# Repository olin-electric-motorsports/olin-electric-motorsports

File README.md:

<h1 align="center">
	
</h1>

Welcome to the Olin Electric Motorsports monorepo. This is the home for all of our
electrical, firmware, and software work.

This document will help you get started contributing and walk you through
important steps for collaborating with teammates.

## Getting Started

### For new members:
Make sure you have a GitHub account. If you don't, create one on [GitHub](github.com) (this website). Make sure to save your username, email, and password. This will be useful in the next step. Once you have an account, STOP, and ask a lead/senior engineer to add you to the `olin-electric-motorsports` org.

Once you've successfully installed Ubuntu, have a GitHub account, and have ben added as an org member: on your computer, open a terminal (press the Windows key and type `term`, then hit `Enter`).

Install `git` on your computer if it's not already.
```shell
sudo apt install git -y
```

Also install python3.10
```shell
sudo apt update && sudo apt install python3.10
```

One last Python library...
```shell
sudo apt-get install python3-distutils
```

### Linking a Computer to your Account
We need to connect your GitHub account to your computer's specific git instance \(created by the command you just ran\). We do this for safety: someone pretending to be you can't add code to our repo!
1. Set your username:
```shell
git config --global user.name 'your username here'
```

2. Set your email address:
```shell
git config --global user.email 'your email here'
```

3. Create the SSH Key \(essentially a super crazy passord\). When you’re prompted to "Enter a file in which to save the key," press `Enter`. This accepts the default file location. At the password prompt, hit `Enter` again.
```shell
ssh-keygen -t ed25519 -C "your_email@example.com"
```

4. To see your SSH Key, run the following command. Copy the whole contents of the output to your clipboard (you won't be able to copy or paste in the terminal using ctrl+c and ctrl+v, instead use ctrl+shift+c and ctrl+shift+v or right-click to do it graphically).
```shell
cat ~/.ssh/id_ed25519.pub
```

5. In your github page, go to your profile \(Top Right\) > `settings` > `SSH and GPG Keys`. Click on the green `New SSH Key` button. Title your key as `Olin Computer` and paste in your SSH key. Finally, click the green `Add SSH Key` button. Nearly done!
6. Test your ssh connection by using the command below. Type `yes` when prompted. You've done this step correctly if you see something along the lines of `Hi "username"! You've successfully authenticated, but GitHub does not provide shell access.`
```shell
ssh -T git@github.com
```
### Creating your OEM environment
Clone this repository into a folder of your choice (many people
choose to put it in `~/Documents`.

```shell
cd ~/Documents
git clone git@github.com:olin-electric-motorsports/olin-electric-motorsports.git
```

Once you have it, cd into the repo and install the KiCad Git filters (a set of rules that remove temp files that can cause clutter):

```shell
cd olin-electric-motorsports/
./scripts/install_kicad_git_filters.sh
```

You'll also want to have the KiCad Git Hooks to generate our symbol libraries. These hooks run every time you push or pull and allow multiple users to add symbols/footprints to our KiCAD library.

```shell
./scripts/install_kicad_git_hooks.sh
```

### Installing AVR and tools
Next, install the AVR toolchain:

```shell
sudo apt install gcc-avr avrdude avr-libc binutils-avr gdb-avr
```

### Installing Cantools
You need to be able to hear to our MCUs on the car!
```shell
pip3 install cantools
sudo apt install can-utils
```

### Installing Bazel

Next, install Bazelisk. Run this massive blob and you should be good to go.

```shell
sudo apt install apt-transport-https curl gnupg -y
curl -fsSL https://bazel.build/bazel-release.pub.gpg | gpg --dearmor >bazel-archive-keyring.gpg
sudo mv bazel-archive-keyring.gpg /usr/share/keyrings
echo "deb [arch=amd64 signed-by=/usr/share/keyrings/bazel-archive-keyring.gpg] https://storage.googleapis.com/bazel-apt stable jdk1.8" | sudo tee /etc/apt/sources.list.d/bazel.list
sudo apt install bazel-5.4.0
```

You should now be able to run the following without error (after changing your directory to be in
the `olin-electric-motorsports` folder):

```shell
bazel build --config=16m1 //examples/16M1/blinky -c opt
```

> [!NOTE]
> If you get an error message stating 'env: python: No such file or directory', ensure that the PATH environment variable is properly established. This can be done by adding the file to your .bashrc file:
> ```
> export PATH=$PATH:/usr/local/bin
> ```

### KiCad Setup

To install KiCad on Ubuntu, run the following: Type `Y` when prompted.

```shell
sudo add-apt-repository --yes ppa:kicad/kicad-8.0-releases
sudo apt update
sudo apt install --install-recommends kicad
```

Open KiCad (windows key and type KiCAD) Click on the Blue App (always do this when opening Kicad - otherwise you can corrupt files!). Hit `Enter` if asked about settings imports and auto-updates for add-ons.
From the top bar, open _Preferences > Configure Paths..._. Add a new row to the table using the plus button (you will have to fill out TWO fields... shown below):

Name | Path
-----|-----
OEM\_DIR|`/home/your-username/Documents/olin-electric-motorsports`

Click `OK`, then again from the top bar, open _Preferences > Manage Symbol Libraries ..._.
Same deal as before with the new line at the bottom, new values though this time:

Name | Path
-----|-----
OEM |`${OEM_DIR}/parts/schematic/oem.kicad_sym`

> [!WARNING]
> If you get an error, you either typed something incorrectly or haven't generated the OEM symbol library ever before.
> To generate:
> 1. navigate to the base `olin-electric-motorsports` directory in a terminal.
> 2. run python3 tools/symbols/convert.py symbols2library
> 3. path to symbol files: parts/schematic/oem
> 4. path to library file: parts/schematic/oem.kicad_sym

Click `OK`, then again from the top bar, open _Preferences > Manage Footprint Libraries ..._.
3rd time's the magic one, plus button, add the values in the table below.

Name | Path
-----|-----
OEM |`${OEM_DIR}/parts/oem.pretty`

where `your-username` is the username on your computer.
If you cloned our repository into a different directory than the `~/Documents` folder, this is just an absolute path to the repo.

Visit [this page](https://www.kicad.org/download/) to find instructions for
downloading KiCad for other operating systems.

## Integration Resources
### Flashing to microcontrollers

> [!CAUTION]
> Take care to plug in the programmer correctly. If you insert it the wrong way, you have the potential to reverse-bias sensitive electronics (you could smoke them)!

To flash (program) an ATMEGA16m1 microcontroller, use a variation of the following command:
```shell
need to insert example flashing command here
```

To flash (program) an ATMEGA16m1 microcontroller using the btldr (remote CAN flashing), use a variation of the following command:
```shell
need to insert example can flashing command here
```

### Viewing CAN data/the canviewer
First, plug a CAN-to-USB dongle into your computer and connect CAN+ and CAN- to the car or test platform's CAN port.

To initalize the dongle, run the following command:
```shell
need to insert example can init command here
```

### Cantools
1. `candump`: A tool for streaming CAN frames as they are sent. Useful for short captures or slow data.
2. `cansniffer`: Similar to candump, but messages with the same ID replace each other for easier viewing (a table).
3. `cansend`: Use this tool to send CAN frames from your computer. CAN (oh the puns will never end) be helpful when debugging boards or to program modules like the motor controller or G-Meter.

### CANViewer
OEM has designed a custom Python CAN GUI to monitor the car's state.
Type the following command to run the viewer.
```shell
need to insert CANViewer command here.
```

### Contributing

If you are working on a new project, the first step is to make sure you have the
latest code:

```shell
git pull origin main
```

### Onboarding stop here...

Next, create your feature branch (only do this once you have a project!):

```shell
git switch -c your-username/feature-name origin/main
```

Now, you can start working on code, committing on your branch, and eventually
opening up a pull request to `main`.

New projects should be placed into a folder within the `//projects` directory
(for instance, `//projects/hitl/`. Hardware and firmware that run on MKV or MKVI
should go in the proper subfolder within `//vehicle`.

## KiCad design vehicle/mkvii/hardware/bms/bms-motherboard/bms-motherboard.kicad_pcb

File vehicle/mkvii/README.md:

# MKVII

The development of boards for the Mark VII car will go in this folder.
Here's to a great year everyone!

Rev. 1: Hardware complete as of 3/9/2025! Subteam folders have their boards inside.
Rev. 2: Software build-out in progress. As of 3/9/2025 the basic folder structure exists!

Useful commands:
1. Setting up a CANnable: `sudo ip link set can0 up type can bitrate 500000`
2. Dumping all CAN commands: `candump can0`
3. Dumping specific commands with a specific address (XXX): `candump can0,XXX:7ff`
4. Quickly viewing many CAN messages in a readable way: `cansniffer can0`
5. using canviewer: `bazel run //projects/canviewer -- -b socketcan -c can0`
6. Flashing an ATMEGA: `SET_FUSES=1 bazel run --config=16m1 -c opt //examples/blinky -- -c usbasp` IF FLASH FAILS, BOARD IS MADE INCORRECTLY. Use `usbasp` for the small programmers, `avrispmkII` for the large blue ones. SET_FUSES=1 required for first flash only.

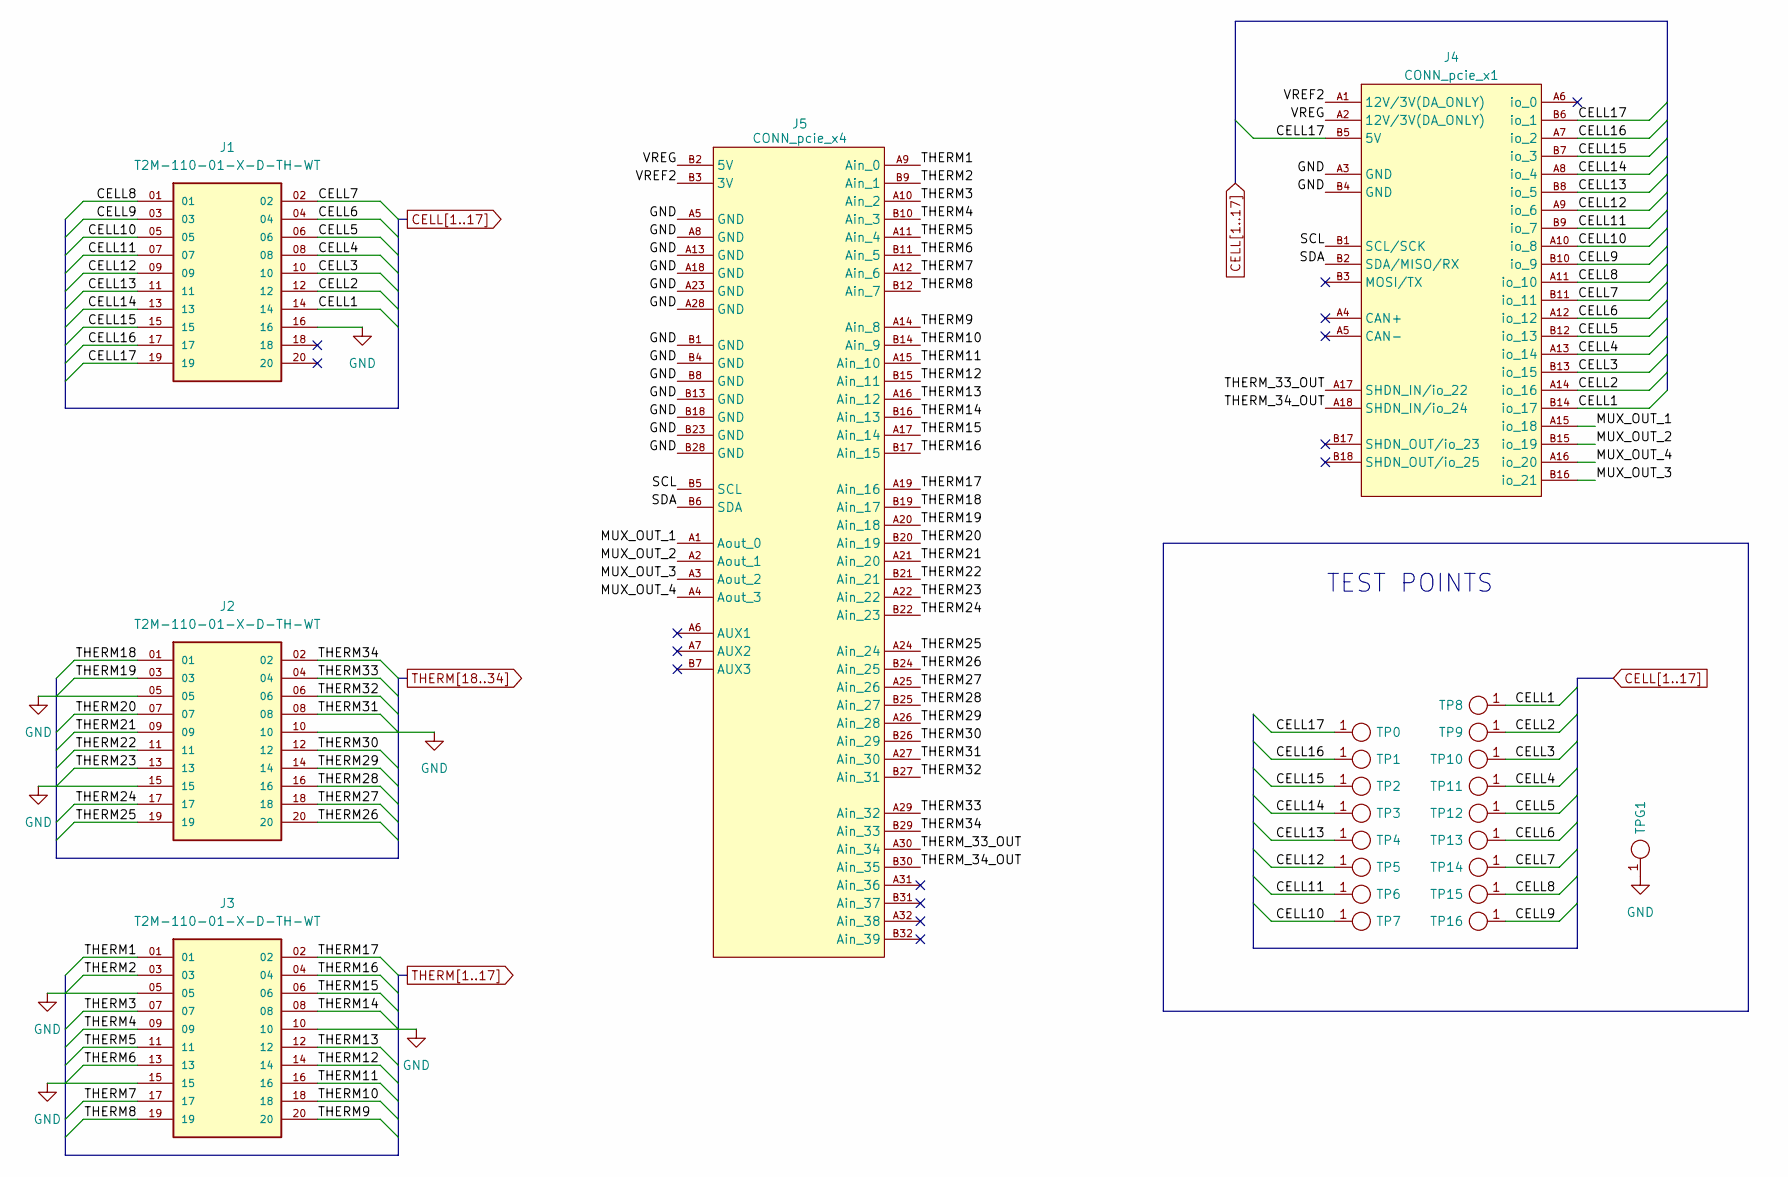
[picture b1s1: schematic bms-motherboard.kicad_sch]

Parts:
J1, J2, J3: T2M-110-01-X-D-TH-WT; SAMTEC_T2M-110-01-X-D-TH-WT; PARTREV AH
J4: CONN_pcie_x1; te_pcie_x1_connector
J5: CONN_pcie_x4; te_pcie_x4_connector
TP0, TP1, TP2, TP3, TP4, TP5, TP6, TP7, TP8, TP9, TP10, TP11, TP12, TP13, TP14, TP15, TP16: TP_SMD; Test_Point_SMD; MPN 5019
TPG1: TP_SMD; Test_Point_SMD; MPN 5019

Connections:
/MUX_OUT_1: J4.A15 (io_18), J5.A1 (Aout_0)
/MUX_OUT_2: J4.B15 (io_19), J5.A2 (Aout_1)
/MUX_OUT_3: J4.B16 (io_21), J5.A3 (Aout_2)
/MUX_OUT_4: J4.A16 (io_20), J5.A4 (Aout_3)
/SCL: J4.B1 (SCL/SCK), J5.B5 (SCL)
/SDA: J4.B2 (SDA/MISO/RX), J5.B6 (SDA)
/THERM_33_OUT: J4.A17 (SHDN_IN/io_22), J5.A30 (Ain_34)
/THERM_34_OUT: J4.A18 (SHDN_IN/io_24), J5.B30 (Ain_35)
/VREF2: J4.A1 (12V/3V(DA_ONLY)), J5.B3 (3V)
/VREG: J4.A2 (12V/3V(DA_ONLY)), J5.B2 (5V)
CELL1: J1.14, J4.B14 (io_17), TP8.1
CELL2: J1.12, J4.A14 (io_16), TP9.1
CELL3: J1.10, J4.B13 (io_15), TP10.1
CELL4: J1.08, J4.A13 (io_14), TP11.1
CELL5: J1.06, J4.B12 (io_13), TP12.1
CELL6: J1.04, J4.A12 (io_12), TP13.1
CELL7: J1.02, J4.B11 (io_11), TP14.1
CELL8: J1.01, J4.A11 (io_10), TP15.1
CELL9: J1.03, J4.B10 (io_9), TP16.1
CELL10: J1.05, J4.A10 (io_8), TP7.1
CELL11: J1.07, J4.B9 (io_7), TP6.1
CELL12: J1.09, J4.A9 (io_6), TP5.1
CELL13: J1.11, J4.B8 (io_5), TP4.1
CELL14: J1.13, J4.A8 (io_4), TP3.1
CELL15: J1.15, J4.B7 (io_3), TP2.1
CELL16: J1.17, J4.A7 (io_2), TP1.1
CELL17: J1.19, J4.B5 (5V), J4.B6 (io_1), TP0.1
GND: J1.16, J2.05, J2.10, J2.15, J3.05, J3.10, J3.15, J4.A3 (GND), J4.B4 (GND), J5.A5 (GND), J5.A8 (GND), J5.A13 (GND), J5.A18 (GND), J5.A23 (GND), J5.A28 (GND), J5.B1 (GND), J5.B4 (GND), J5.B8 (GND), J5.B13 (GND), J5.B18 (GND), J5.B23 (GND), J5.B28 (GND), TPG1.1; also elsewhere on the board
THERM1: J3.01, J5.A9 (Ain_0)
THERM2: J3.03, J5.B9 (Ain_1)
THERM3: J3.07, J5.A10 (Ain_2)
THERM4: J3.09, J5.B10 (Ain_3)
THERM5: J3.11, J5.A11 (Ain_4)
THERM6: J3.13, J5.B11 (Ain_5)
THERM7: J3.17, J5.A12 (Ain_6)
THERM8: J3.19, J5.B12 (Ain_7)
THERM9: J3.20, J5.A14 (Ain_8)
THERM10: J3.18, J5.B14 (Ain_9)
THERM11: J3.16, J5.A15 (Ain_10)
THERM12: J3.14, J5.B15 (Ain_11)
THERM13: J3.12, J5.A16 (Ain_12)
THERM14: J3.08, J5.B16 (Ain_13)
THERM15: J3.06, J5.A17 (Ain_14)
THERM16: J3.04, J5.B17 (Ain_15)
THERM17: J3.02, J5.A19 (Ain_16)
THERM18: J2.01, J5.B19 (Ain_17)
THERM19: J2.03, J5.A20 (Ain_18)
THERM20: J2.07, J5.B20 (Ain_19)
THERM21: J2.09, J5.A21 (Ain_20)
THERM22: J2.11, J5.B21 (Ain_21)
THERM23: J2.13, J5.A22 (Ain_22)
THERM24: J2.17, J5.B22 (Ain_23)
THERM25: J2.19, J5.A24 (Ain_24)
THERM26: J2.20, J5.B24 (Ain_25)
THERM27: J2.18, J5.A25 (Ain_26)
THERM28: J2.16, J5.B25 (Ain_27)
THERM29: J2.14, J5.A26 (Ain_28)
THERM30: J2.12, J5.B26 (Ain_29)
THERM31: J2.08, J5.A27 (Ain_30)
THERM32: J2.06, J5.B27 (Ain_31)
THERM33: J2.04, J5.A29 (Ain_32)
THERM34: J2.02, J5.B29 (Ain_33)

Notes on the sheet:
TEST POINTS

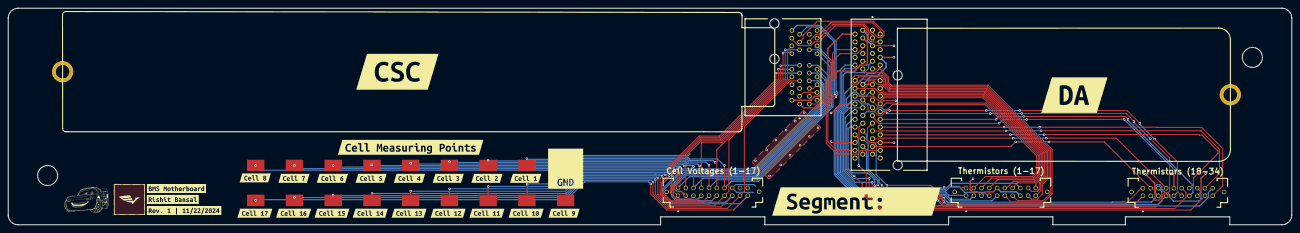
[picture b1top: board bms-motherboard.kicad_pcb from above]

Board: 2 copper layers, 331.3 x 55.9 mm, 50 parts (0 on the bottom side), 62 nets.

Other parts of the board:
H1, H2: CONN_MountingHole; PCIe_Mount
kibuzzard-6747A1EF: G***; kibuzzard-6747A1EF
kibuzzard-6747A1F5: G***; kibuzzard-6747A1F5
kibuzzard-6747A1FA: G***; kibuzzard-6747A1FA
kibuzzard-6747A20D: G***; kibuzzard-6747A20D
kibuzzard-6747A21A: G***; kibuzzard-6747A21A
kibuzzard-6747A21D: G***; kibuzzard-6747A21D
kibuzzard-6747A22C: G***; kibuzzard-6747A22C
kibuzzard-6747A22F: G***; kibuzzard-6747A22F
kibuzzard-6747A069: G***; kibuzzard-6747A069
kibuzzard-6747A200: G***; kibuzzard-6747A200
kibuzzard-6747A204: G***; kibuzzard-6747A204
kibuzzard-6747A209: G***; kibuzzard-6747A209
kibuzzard-6747A211: G***; kibuzzard-6747A211
kibuzzard-6747A215: G***; kibuzzard-6747A215
kibuzzard-6747A222: G***; kibuzzard-6747A222
kibuzzard-6747A229: G***; kibuzzard-6747A229
kibuzzard-6747A234: G***; kibuzzard-6747A234
kibuzzard-6747A319: G***; kibuzzard-6747A319
kibuzzard-6747A384: G***; kibuzzard-6747A384
kibuzzard-6747F2A5: G***; kibuzzard-6747F2A5
kibuzzard-67479DDA: G***; kibuzzard-67479DDA
kibuzzard-67479DE7: G***; kibuzzard-67479DE7
kibuzzard-67479E06: G***; kibuzzard-67479E06
kibuzzard-67479E66: G***; kibuzzard-67479E66
kibuzzard-67479E86: G***; kibuzzard-67479E86

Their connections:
GND: H2.1; also elsewhere on the board

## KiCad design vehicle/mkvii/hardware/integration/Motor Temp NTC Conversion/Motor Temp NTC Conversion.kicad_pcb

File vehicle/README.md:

# Vehicle

The boards and code for the different vehicles that the team builds will exist
in this folder.

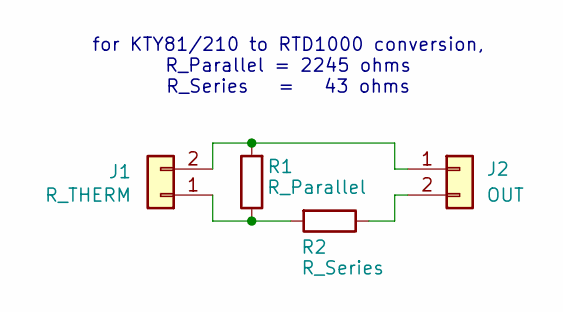
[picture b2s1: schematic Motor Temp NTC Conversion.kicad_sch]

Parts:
J1: R_THERM; Molex_Micro-Fit_3.0_43650-0215_1x02_P3.00mm_Vertical
J2: OUT; Molex_Micro-Fit_3.0_43650-0215_1x02_P3.00mm_Vertical
R1: R_Parallel; R_0603; MPN RMCF0603FT1K00
R2: R_Series; R_0603; MPN RMCF0603FT1K00

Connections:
unnamed: J1.1, R1.1, R2.2
unnamed: J1.2, J2.1, R1.2
unnamed: J2.2, R2.1

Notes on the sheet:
for KTY81/210 to RTD1000 conversion, R_Parallel = 2245 ohms R_Series = 43 ohms

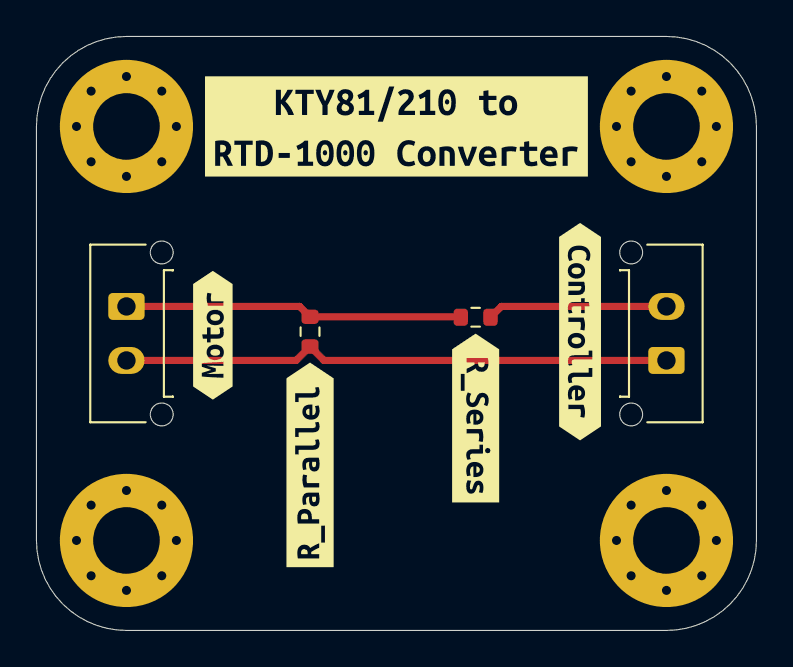
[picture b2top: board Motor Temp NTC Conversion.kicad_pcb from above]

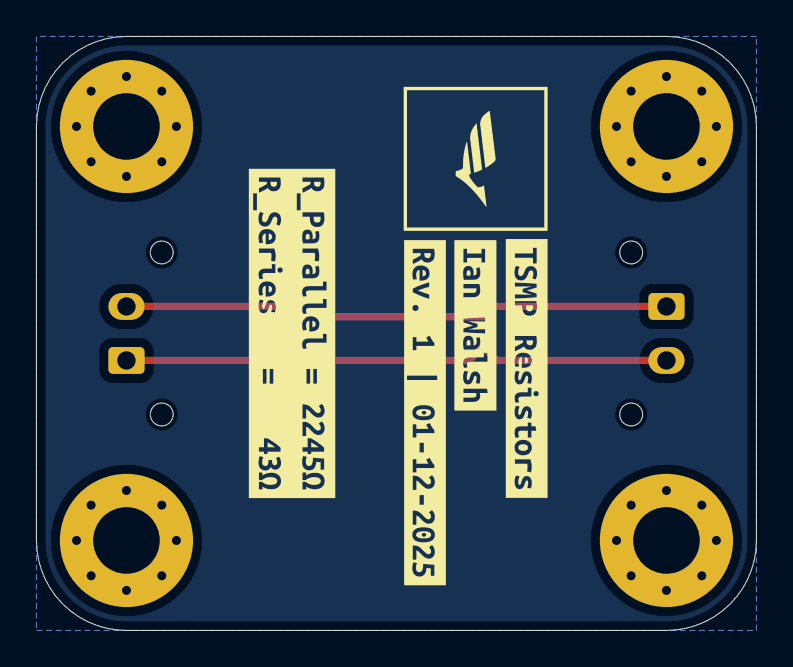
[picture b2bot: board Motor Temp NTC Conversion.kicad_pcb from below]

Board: 2 copper layers, 40.0 x 33.0 mm, 13 parts (4 on the bottom side), 3 nets.

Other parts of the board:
kibuzzard-679ED0A2: G***; kibuzzard-679ED0A2
kibuzzard-679ED03B: G***; kibuzzard-679ED03B
kibuzzard-679ED07E: G***; kibuzzard-679ED07E
kibuzzard-679ED063: G***; kibuzzard-679ED063
kibuzzard-679ED130: G***; kibuzzard-679ED130
kibuzzard-679FBE94: G***; kibuzzard-679FBE94
kibuzzard-678424C4: G***; kibuzzard-678424C4
kibuzzard-6784247E: G***; kibuzzard-6784247E
kibuzzard-67842498: G***; kibuzzard-67842498

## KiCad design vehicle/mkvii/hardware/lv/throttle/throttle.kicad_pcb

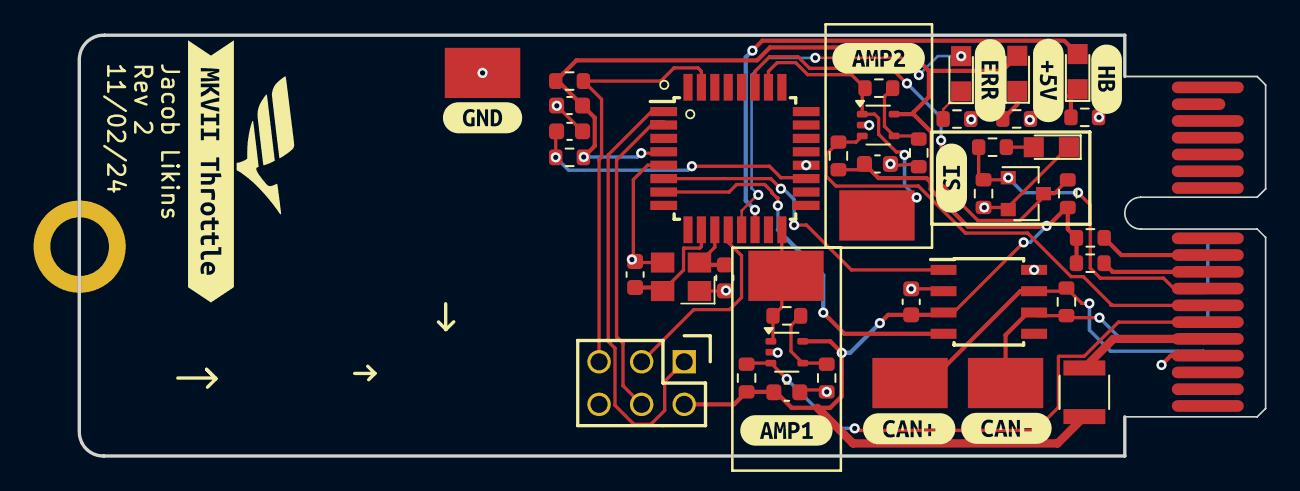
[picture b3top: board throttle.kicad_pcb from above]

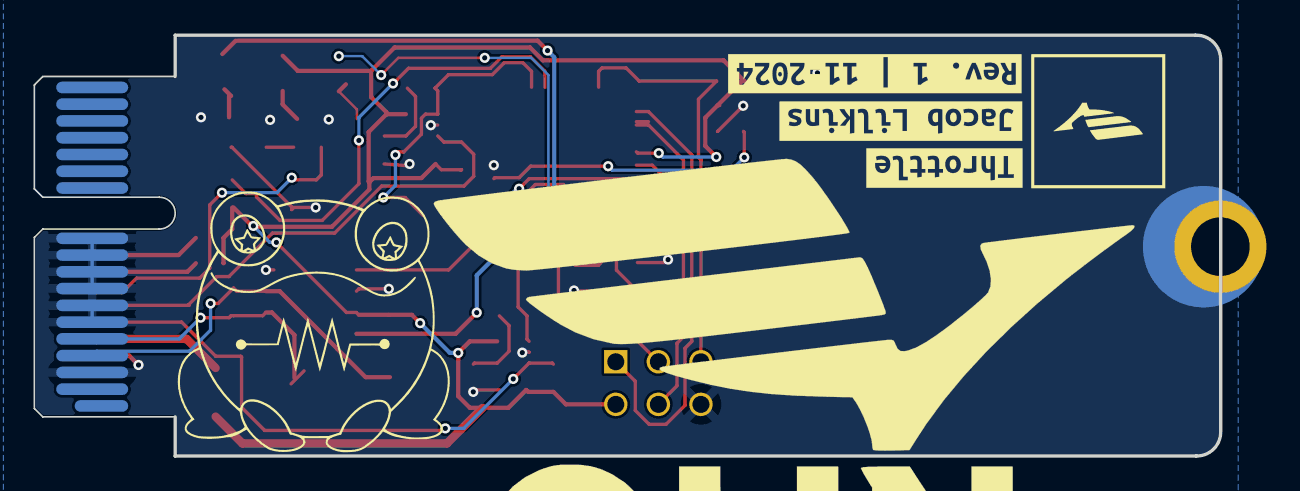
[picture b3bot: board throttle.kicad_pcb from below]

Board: 2 copper layers, 70.8 x 25.1 mm, 56 parts (3 on the bottom side), 30 nets.

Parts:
C1, C2, C3, C7: 0.1uF; C_0603
C4: C_100pF; C_0603
C5, C6: C_30pF; C_0603
D1: LED_BLUE; CHIPLED_0805
D2, D4: LED_AMBER; CHIPLED_0805
D3: LED_WHITE; CHIPLED_0805
F1: F_500mA_16V; Fuse_1210
IP1: TP_1mm; Test_Point_SMD
J2: CONN_02x03; Pin_Header_Straight_2x03
J4: CONN_pcie_x1; pcie_x1
Q1: SSM3K333R; SOT-23F
R1, R4: R_1M; R_0603
R2, R5, R11: R_0; R_0603
R3, R6: R_2.2K; R_0603
R7: 3KR; R_0603
R8: R_100K; R_0603
R9, R13, R17: R_10K; R_0603
R10, R15, R16: 1KR; R_0603
R12: R_100; R_0603
R14: R_120_DNP; R_0603
TP1, TP2: TP_SMD; Test_Point_SMD
TP3: CANL1; Test_Point_SMD
TP4: CANH1; Test_Point_SMD
U1, U2: MCP6001; SOT-353_SC-70-5
U3: ATMEGA16M1; TQFP-32_7x7mm_Pitch0.8mm
U4: MAX33011EASA; SOIC-8_3.9x4.9mm_Pitch1.27mm_OEM
U$2: M.2_Mount
Y1: Crystal_16MHz_18pF; Crystal_TXC7M
kibuzzard-673BD4E0: G***; kibuzzard-673BD4E0
kibuzzard-673BD4E9: G***; kibuzzard-673BD4E9
kibuzzard-673BD5FE: G***; kibuzzard-673BD5FE
kibuzzard-673BD9A5: G***; kibuzzard-673BD9A5
kibuzzard-673BDF62: G***; kibuzzard-673BDF62
kibuzzard-673C1B3F: G***; kibuzzard-673C1B3F
kibuzzard-673C1B36: G***; kibuzzard-673C1B36
kibuzzard-673C1C01: G***; kibuzzard-673C1C01
kibuzzard-673C17D4: G***; kibuzzard-673C17D4
kibuzzard-673C17DA: G***; kibuzzard-673C17DA
kibuzzard-673C162B: G***; kibuzzard-673C162B
kibuzzard-673C189F: G***; kibuzzard-673C189F
kibuzzard-6726AB29: G***; kibuzzard-6726AB29

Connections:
+5V: C1.1, C2.1, C3.1, C7.1, D3.2 (A), F1.1, J2.2, R1.1, R4.1, R9.1, R11.1, R12.1, R13.1, R17.1, U1.5 (V+), U2.5 (V+), U3.4 (VCC), U4.3 (VDD)
/ Shutdown Sense Inertial Switch/SS_INERTIA_OUTPUT: Q1.3 (D), R9.2, U3.27 ((PCINT6/ADC7/PSCOUT1B)PB6)
/INPUT_THROTTLE_1: J4.B6 (io_1), R1.2, U1.3 (+)
/INPUT_THROTTLE_2: J4.B7 (io_3), R4.2, U2.3 (+)
/Microcontroller/CAN_+: J4.A4 (CAN+), R14.1, TP4.1, U4.7 (CANH)
/Microcontroller/CAN_-: J4.A5 (CAN-), R14.2, TP3.1, U4.6 (CANL)
/Microcontroller/CAN_RX: U3.7 ((PCINT11/T1/ICP1B/RXCAN)PC3), U4.4 (RXD)
/Microcontroller/CAN_TX: U3.6 ((PCINT10/T0/TXCAN)PC2), U4.1 (TXD)
/Microcontroller/HEARTBEAT: D2.2 (A), U3.14 ((PCINT22/ADC3/INT0/ACMPN2)PD6)
/Microcontroller/MISO: J2.1, U3.1 ((PCINT18/PSCIN2/OC1A/MISO_A)PD2)
/Microcontroller/MOSI: J2.4, U3.2 ((PCINT19/TXD/TXLIN/OC0A/~SS/MOSI_A)PD3)
/Microcontroller/OUTPUT_THROTTLE_1: R2.1, TP1.1, U1.1, U3.16 ((PCINT2/ADC5/INT1/ACMPN0)PB2)
/Microcontroller/OUTPUT_THROTTLE_2: R5.1, TP2.1, U2.1, U3.26 ((PCINT5/ADC6/INT2/ACMPN1/AMP2-)PB5)
/Microcontroller/RESET: J2.5, R13.2, U3.31 ((PCINT24/OCD/~RESET)PE0)
/Microcontroller/SCK: J2.3, U3.12 ((PCINT20/ADC1/RXD/RXLIN/ICP1A/SCK_A)PD4)
/Microcontroller/THROTTLE_DISABLE: D4.2 (A), U3.13 ((PCINT21/ADC2/ACMP2)PD5)
/SS_INERTIA_SWITCH: J4.B8 (io_5), Q1.1 (G), R7.2, R8.1
/THROTTLE_1+: J4.B9 (io_7), R17.2
/THROTTLE_2+: J4.B10 (io_9), R11.2
GND: C1.2, C2.2, C3.2, C4.2, C5.2, C6.2, C7.2, D1.1 (K), IP1.1, J2.6, J4.A3 (GND), J4.A6 (io_0), J4.A7 (io_2), J4.A8 (io_4), J4.A9 (io_6), J4.A10 (io_8), J4.A11 (io_10), J4.B4 (GND), Q1.2 (S), R3.2, R6.2, R8.2, R10.2, R15.2, R16.2, U1.2 (V-), U2.2 (V-), U3.5 (GND), U3.20 (AGND), U4.2 (VSS), U4.8 (STBY), U$2.1, Y1.2, Y1.4
unnamed: D1.2 (A), R7.1
unnamed: D2.1 (K), R15.1
unnamed: D3.1 (K), R16.1
unnamed: D4.1 (K), R10.1
unnamed: F1.2, J4.B5 (5V)
unnamed: R2.2, R3.1, U1.4 (-)
unnamed: R5.2, R6.1, U2.4 (-)
unnamed: C6.1, U3.10 ((PCINT25/OC0B/XTAL1)PE1), Y1.3
unnamed: C5.1, U3.11 ((PCINT26/ADC0/XTAL2)PE2), Y1.1
unnamed: C4.1, R12.2, U3.19 (AVCC)

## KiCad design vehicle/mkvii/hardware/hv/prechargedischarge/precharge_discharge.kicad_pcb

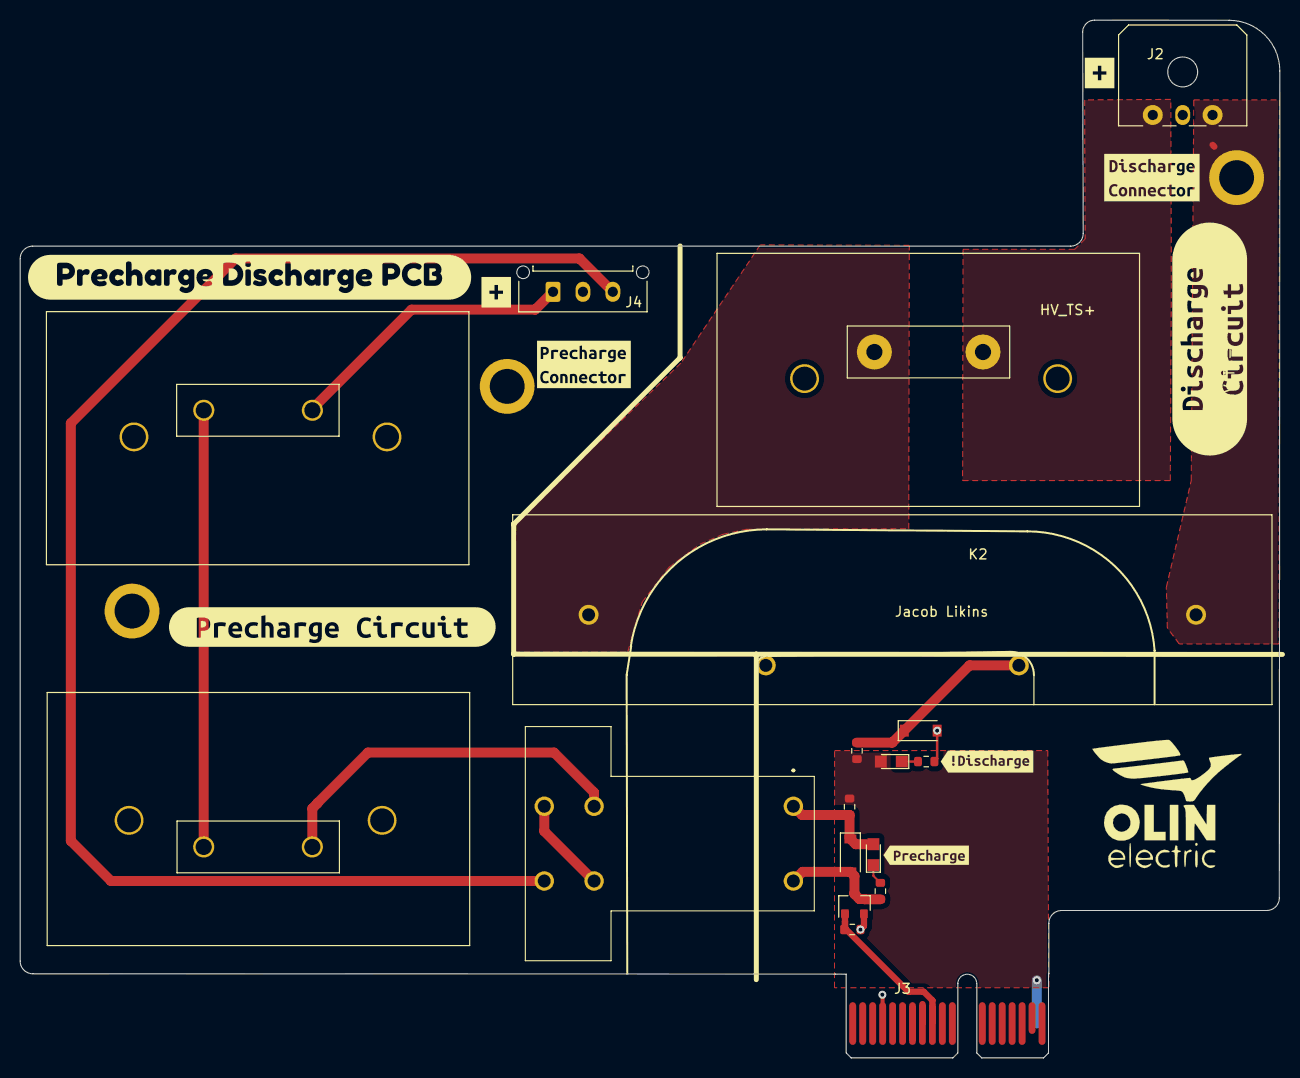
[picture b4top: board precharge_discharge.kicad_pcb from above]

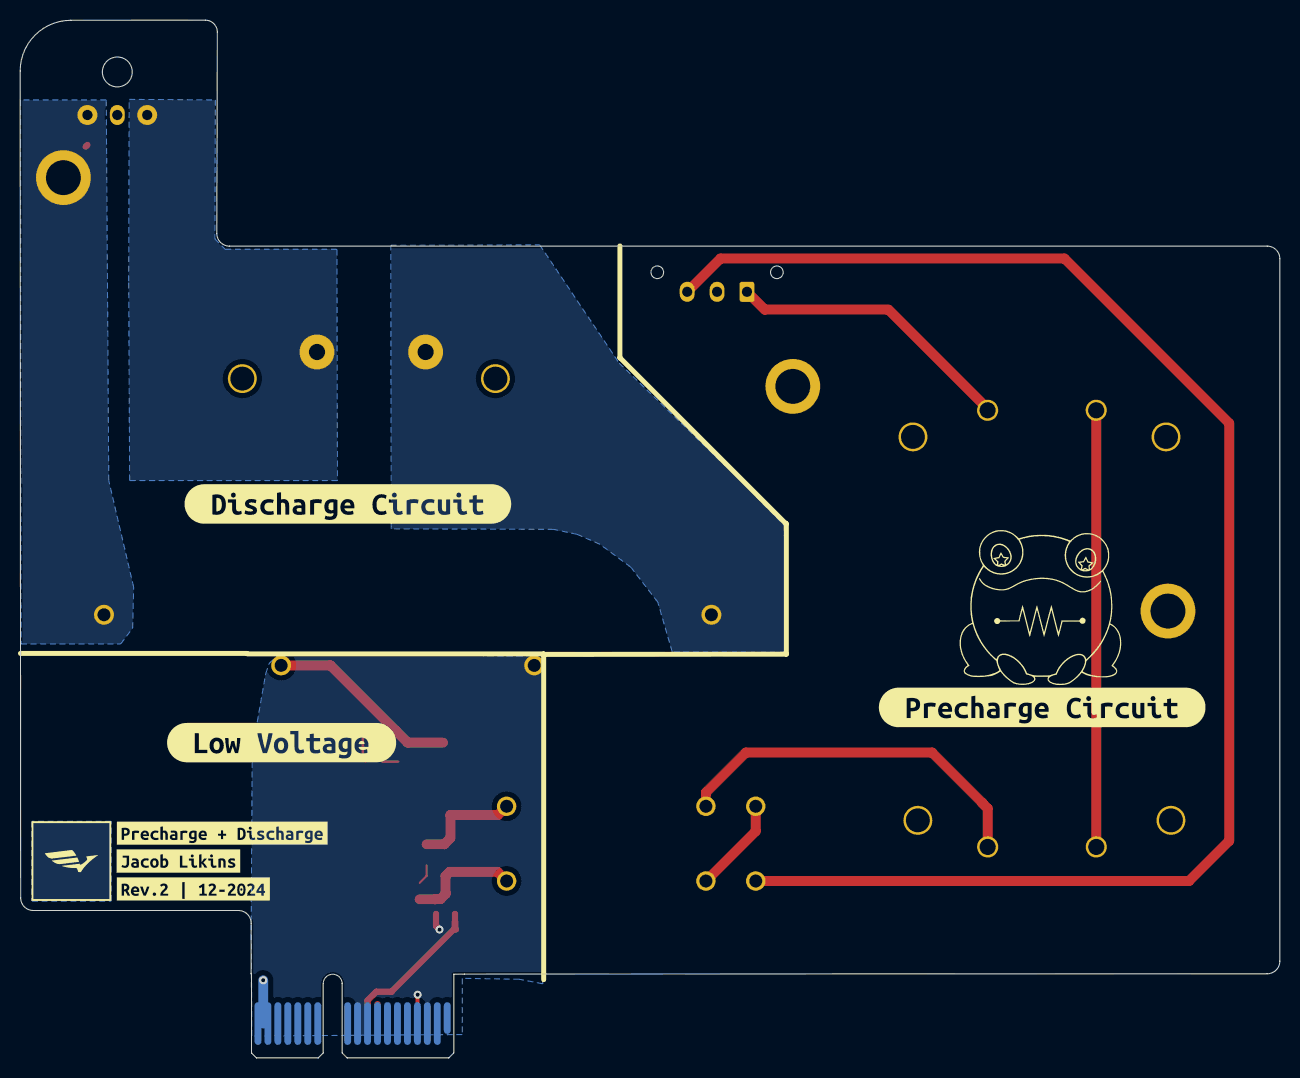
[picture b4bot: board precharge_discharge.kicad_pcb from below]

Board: 2 copper layers, 126.4 x 104.1 mm, 33 parts (6 on the bottom side), 16 nets.

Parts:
D1, D3: SS110LW; D_SOD-123
D2, D4: LED_WHITE; CHIPLED_0805
J2: Conn_01x03_Pin; Molex_Micro-Fit_3.0_43650-0300_1x03_P3.00mm_Horizontal
J3: CONN_pcie_x1; pcie_x1
J4: Conn_01x03_Pin; Molex_Micro-Fit_3.0_43650-0315_1x03_P3.00mm_Vertical
K1: G2RG-2A-X_DC12; G2RG-X
K2: 3350-4275-126; Relay_Comus_3350
Q1: SSM3K333R; SOT-23F
R1: 10KR; R_0603
R2, R5: 12R; R_0603
R3, R4: 560R-100W; R_TO247-Heatsink
R6: 3KR-100W; R_TO247-Heatsink
R7, R8: 1KR; R_0603
kibuzzard-679E7E49, kibuzzard-679E7E49#2: G***; kibuzzard-679E7E49
kibuzzard-679E7E71: G***; kibuzzard-679E7E71
kibuzzard-679E7EA1: G***; kibuzzard-679E7EA1
kibuzzard-679E816B: G***; kibuzzard-679E816B
kibuzzard-679E8163: G***; kibuzzard-679E8163
kibuzzard-679E8270: G***; kibuzzard-679E8270
kibuzzard-679EBF0B, kibuzzard-679EBF0B#2: G***; kibuzzard-679EBF0B
kibuzzard-6784D6A3: G***; kibuzzard-6784D6A3
kibuzzard-6784D6E2: G***; kibuzzard-6784D6E2
kibuzzard-6784D6F7: G***; kibuzzard-6784D6F7
kibuzzard-6784D72B: G***; kibuzzard-6784D72B
kibuzzard-6784D698: G***; kibuzzard-6784D698
kibuzzard-639639B8: G***; kibuzzard-639639B8

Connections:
/FINAL_SHUTDOWN: D2.2 (A), J3.A17 (SHDN_IN/io_22), J3.A18 (SHDN_IN/io_24), R2.1, R5.1
/HV_BAT+: J4.1, R4.1
/HV_TS+: J2.1, R6.1
/HV_TS+_Fuse: J4.3, K1.5 (NO_(-))
/HV_TS-: J2.3, K2.1
/PRECHARGE_LSD: J3.B9 (io_7), Q1.1 (G), R1.1
GND: D3.2 (A), J3.A3 (GND), J3.A9 (io_6), J3.A10 (io_8), J3.B4 (GND), K2.3 (-), Q1.2 (S), R1.2, R7.2
unnamed: D1.2 (A), K1.8 (COIL_2), Q1.3 (D), R8.2
unnamed: D1.1 (K), D4.2 (A), K1.1 (COIL_1), R2.2
unnamed: D2.1 (K), R7.1
unnamed: D3.1 (K), K2.2 (+), R5.2
unnamed: D4.1 (K), R8.1
unnamed: K1.4 (NO), K1.6 (COM)
unnamed: K1.3 (COM_(+)), R3.2
unnamed: K2.4, R6.2
unnamed: R3.1, R4.2

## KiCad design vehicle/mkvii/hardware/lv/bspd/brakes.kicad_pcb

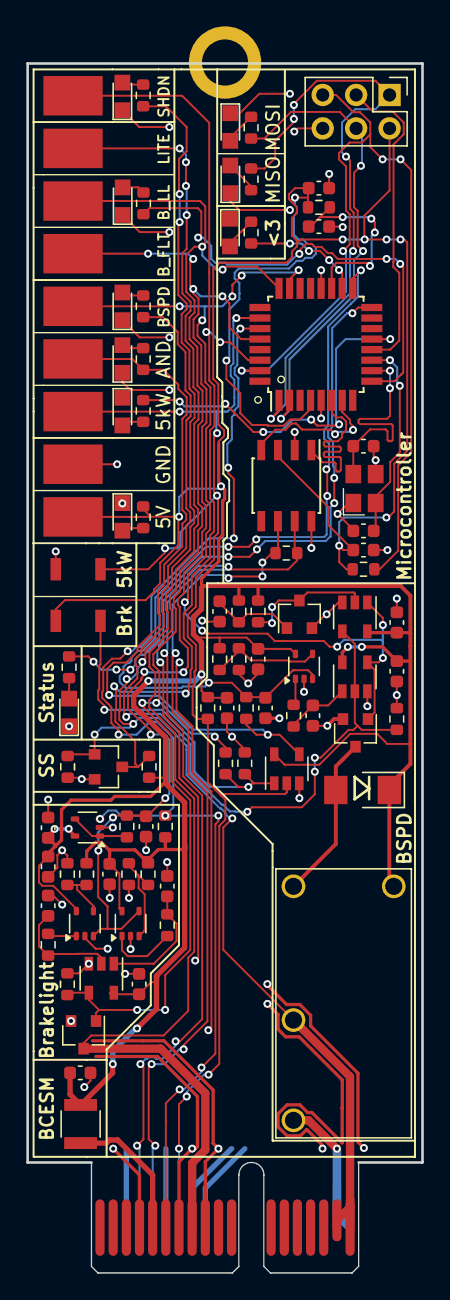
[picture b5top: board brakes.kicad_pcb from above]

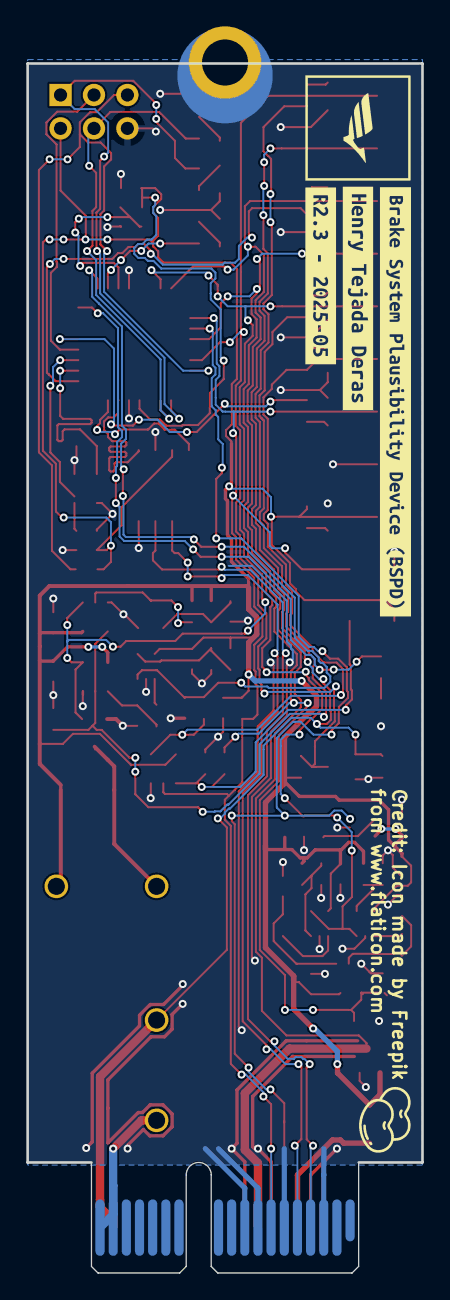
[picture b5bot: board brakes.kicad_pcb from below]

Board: 2 copper layers, 30.0 x 91.9 mm, 99 parts (3 on the bottom side), 54 nets.

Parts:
C1, C3, C4, C5, C8, C9, C10, C11, C13, C14, C20: C_0.1uF; C_0603
C2, C7, C15: C_1uF; C_0603
C6, C21: C_10uF; C_0603
C12: C_0.22uF; C_0603
C16: C_100pF; C_0603
C17, C18: C_15pF; C_0603
D1: BSPD_TRIP_LED; CHIPLED_0805
D2: HEARTBEAT; CHIPLED_0805
D3: BSPD_TRIP; CHIPLED_0805
D4: 5V_LED; CHIPLED_0805
D5: D_Zener_18V_SMBJ5355B-TP; DO-214AA
D6: BSPD_GATE_TRIP; CHIPLED_0805
D7: MISO_PROG_LED; CHIPLED_0805
D8: MOTOR ON; CHIPLED_0805
D9: Shutdown_LED; CHIPLED_0805
D10: BRAKES; CHIPLED_0805
D13: MOSI_PROG_LED; CHIPLED_0805
F1: F_500mA_16V; Fuse_1210
H1: CONN_MountingHole; PCIe_Mount
J1: CONN_pcie_x1; pcie_x1
J3: CONN_02x03; PinHeader_2x03_P2.54mm_Vertical
K2: Relay_G5Q-1A4-DC5; Relay_SPST_OMRON-G5Q-1A4_OEM
Q2, Q3, Q4, Q5: Q_NMOS_SSM3K333R; SOT-23F
R1: R_576; R_0603
R2, R4, R5, R6, R12, R14, R15, R17, R20, R23, R31, R35: R_10K; R_0603
R3, R22: R_100; R_0603
R7: R_120; R_0603
R8, R10, R16, R19, R24, R25, R26, R27, R28, R30, R32: R_1K; R_0603
R9, R11, R18, R34: R_100K; R_0603
R13: R_71.5K; R_0603
R21: R_75K; R_0603
R33: R_3K; R_0603
SW1, SW2: SW_Push_SPST_NO; SW_B3U-1000P_4.2x1.7mm
TP1: B_OT; Test_Point_SMD
TP2: LITE; Test_Point_SMD
TP3: GND; Test_Point_SMD
TP4: BSPD; Test_Point_SMD
TP5: SHDN; Test_Point_SMD
TP7: 5kW; Test_Point_SMD
TP8: B_IN; Test_Point_SMD
TP10: AND; Test_Point_SMD
TP11: 5V; Test_Point_SMD
U1: U_CAN_MCP2561; SOIC-8_3.9x4.9mm_Pitch1.27mm_OEM
U2, U3, U4, U6: U_OPAMP_MCP6001; SOT-353_SC-70-5
U5, U7: U_GATE_SN74LVC1G02DBVR; SOT-23-5_OEM
U8: U_GATE_SN74LVC1G32DBVR; SOT-23-5_OEM
U9: U_GATE_SN74LVC1G08DBVR; SOT-23-5_OEM
U10: U_ATMEGA16M1; TQFP-32_7x7mm_Pitch0.8mm
Y1: X_Crystal_16MHz_18pF; Crystal_TXC7M
kibuzzard-672D6696: G***; kibuzzard-672D6696
kibuzzard-673C20EC: G***; kibuzzard-673C20EC
kibuzzard-683122FC: G***; kibuzzard-683122FC

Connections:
+5V: C1.1, C3.1, C4.1, C5.1, C6.1, C8.1, C9.1, C10.1, C13.1, C14.2, C20.1, D5.1 (K), F1.1, J3.2, K2.5, R1.1, R2.1, R11.1, R12.1, R15.2, R20.1, R22.1, R23.1, R26.2, R31.1, R34.1, SW2.1, TP11.1, U1.3 (VDD), U2.5 (V+), U3.5 (V+), U4.5 (V+), U5.5 (VCC), U6.5 (V+), U7.5 (VCC), U8.5 (VCC), U9.5 (VCC), U10.4 (VCC)
/BSPD/BRAKELIGHT_LL: Q5.1 (G), R6.2, R28.2, TP1.1, U8.4 (out), U10.24 ((PCINT4/AMP0+)PB4)
/BSPD/BSPD_LL: Q3.1 (G), TP4.1, U5.4 (out), U7.1 (in), U10.23 ((PCINT3/AMP0-)PB3)
/BSPD/BSPD_RELAY_IN: J1.A17 (SHDN_IN/io_22), J1.A18 (SHDN_IN/io_24), K2.3
/BSPD/BSPD_RELAY_OUT: J1.B17 (SHDN_OUT/io_23), J1.B18 (SHDN_OUT/io_25), K2.2, Q2.1 (G), R18.1, R33.2
/BSPD/MOTOR_CURRENT_SENSE: J1.A7 (io_2), R34.2, SW1.2, TP7.1, U9.2 (in), U10.26 ((PCINT5/ADC6/INT2/ACMPN1/AMP2-)PB5)
/BSPD/RC_TIMER_STATUS: C21.1, R13.1, U4.3 (+), U10.17 ((PCINT12/ADC8/ACMPN3/AMP1-)PC4)
/BrakeLight/BRAKELIGHT_CONN: J1.B8 (io_5), Q5.3 (D), TP2.1
/BrakeLight/BRAKE_PRESS_SENSE: J1.B6 (io_1), R2.2, U6.3 (+), U10.27 ((PCINT6/ADC7/PSCOUT1B)PB6)
/BrakeLight/BRAKE_PRESS_SENSE_FILTERED: C12.1, R21.2, TP8.1, U2.3 (+), U3.4 (-), U10.28 ((PCINT7/ADC4/SCK/PSCOUT0B)PB7)
/Microcontroller - ATMEGA16M1/5KW_LED: R8.2, U10.13 ((PCINT21/ADC2/ACMP2)PD5)
/Microcontroller - ATMEGA16M1/BRAKE_LL_LED: R19.2, U10.9 ((PCINT1/MOSI/PSCOUT2B)PB1)
/Microcontroller - ATMEGA16M1/BSPD_SHUTDOWN_SENSE: Q2.3 (D), R20.2, TP5.1, U10.30 ((PCINT8/INT3/PSCOUT1A)PC0)
/Microcontroller - ATMEGA16M1/BSPD_TRIP_LED: R16.2, U10.16 ((PCINT2/ADC5/INT1/ACMPN0)PB2)
/Microcontroller - ATMEGA16M1/CAN_+: J1.A4 (CAN+), R7.1, U1.7 (CANH)
/Microcontroller - ATMEGA16M1/CAN_-: J1.A5 (CAN-), R7.2, U1.6 (CANL)
/Microcontroller - ATMEGA16M1/CAN_RX: U1.4 (RXD), U10.7 ((PCINT11/T1/ICP1B/RXCAN)PC3)
/Microcontroller - ATMEGA16M1/CAN_TX: U1.1 (TXD), U10.6 ((PCINT10/T0/TXCAN)PC2)
/Microcontroller - ATMEGA16M1/HEARTBEAT_LED: R24.1, U10.18 ((PCINT13/ADC9/ACMP3/AMP1+)PC5)
/Microcontroller - ATMEGA16M1/MISO: J3.1, R27.2, U10.1 ((PCINT18/PSCIN2/OC1A/MISO_A)PD2)
/Microcontroller - ATMEGA16M1/MOSI: J3.4, R32.2, U10.2 ((PCINT19/TXD/TXLIN/OC0A/~SS/MOSI_A)PD3)
/Microcontroller - ATMEGA16M1/RESET: J3.5, R23.2, U10.31 ((PCINT24/OCD/~RESET)PE0)
/Microcontroller - ATMEGA16M1/SCK: J3.3, U10.12 ((PCINT20/ADC1/RXD/RXLIN/ICP1A/SCK_A)PD4)
GND: C1.2, C2.2, C3.2, C4.2, C5.2, C6.2, C7.2, C8.2, C9.2, C10.2, C11.1, C12.2, C13.2, C14.1, C15.2, C16.2, C17.2, C18.2, C20.2, C21.2, D1.1 (K), D2.1 (K), D3.1 (K), D4.1 (K), D6.1 (K), D7.1 (K), D8.1 (K), D9.1 (K), D10.1 (K), D13.1 (K), H1.1, J1.A3 (GND), J1.A6 (io_0), J1.A8 (io_4), J1.A9 (io_6), J1.B4 (GND), J1.B7 (io_3), J1.B9 (io_7), J3.6, Q2.2 (S), Q3.2 (S), Q4.2 (S), Q5.2 (S), R3.2, R6.1, R9.2, R14.2, R17.2, R18.2, R30.2, SW1.1, TP3.1, U1.2 (VSS), U1.8 (STBY), U2.2 (V-), U3.2 (V-), U4.2 (V-), U5.3 (GND), U6.2 (V-), U7.3 (GND), U8.3 (GND), U9.3 (GND), U10.5 (GND), U10.20 (AGND), Y1.2, Y1.4
unnamed: C2.1, R5.1, U8.2 (in)
unnamed: C7.1, R35.2, U5.1 (in)
unnamed: C15.1, R4.1, U8.1 (in)
unnamed: D1.2 (A), R25.2
unnamed: D2.2 (A), R24.2
unnamed: D3.2 (A), R16.1
unnamed: D4.2 (A), R26.1
unnamed: D5.2 (A), K2.1, Q3.3 (D)
unnamed: D6.2 (A), R10.2
unnamed: D7.2 (A), R27.1
unnamed: D8.2 (A), R8.1
unnamed: D9.2 (A), R33.1
unnamed: D10.2 (A), R19.1
unnamed: D13.2 (A), R32.1
unnamed: F1.2, J1.B5 (5V)
unnamed: Q4.3 (D), R11.2, U7.2 (in)
unnamed: C11.2, Q4.1 (G), R15.1
unnamed: R4.2, U3.1
unnamed: R5.2, U2.1
unnamed: R9.1, R28.1, SW2.2, U9.1 (in)
unnamed: R35.1, U4.1
unnamed: R1.2, R3.1, U2.4 (-)
unnamed: R30.1, R31.2, U3.3 (+)
unnamed: R12.2, R14.1, U4.4 (-)
unnamed: R21.1, U6.1, U6.4 (-)
unnamed: R17.1, R25.1, U5.2 (in), U7.4 (out)
unnamed: R10.1, R13.2, TP10.1, U9.4 (out)
unnamed: C18.1, U10.10 ((PCINT25/OC0B/XTAL1)PE1), Y1.3
unnamed: C17.1, U10.11 ((PCINT26/ADC0/XTAL2)PE2), Y1.1
unnamed: C16.1, R22.2, U10.19 (AVCC)
